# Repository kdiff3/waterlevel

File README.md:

# This is a PCB for a Capacitive Water Level Sensor

## License

This work is licensed under a Creative Commons Attribution-NonCommercial-ShareAlike 4.0 International License.

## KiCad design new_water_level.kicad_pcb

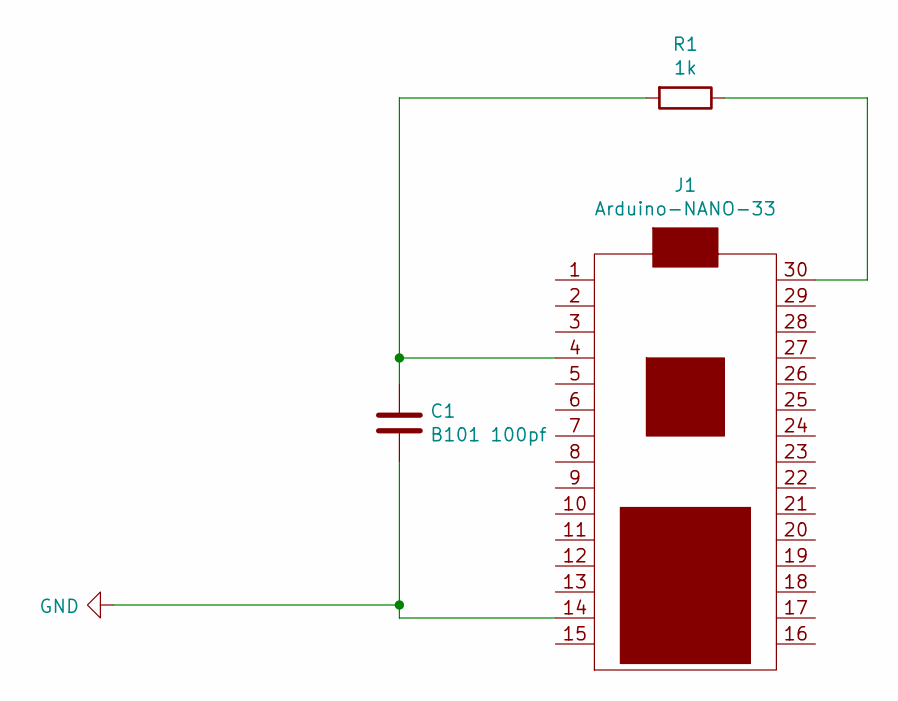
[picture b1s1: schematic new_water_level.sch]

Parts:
C1: B101 100pf; C_Disc_D5.0mm_W2.5mm_P5.00mm
J1: Arduino-NANO-33; NANO_33_Socket_Castell
R1: 1k; R_Axial_DIN0207_L6.3mm_D2.5mm_P10.16mm_Horizontal

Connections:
GND: C1.2, J1.14
unnamed: C1.1, J1.4, R1.2
unnamed: J1.30, R1.1

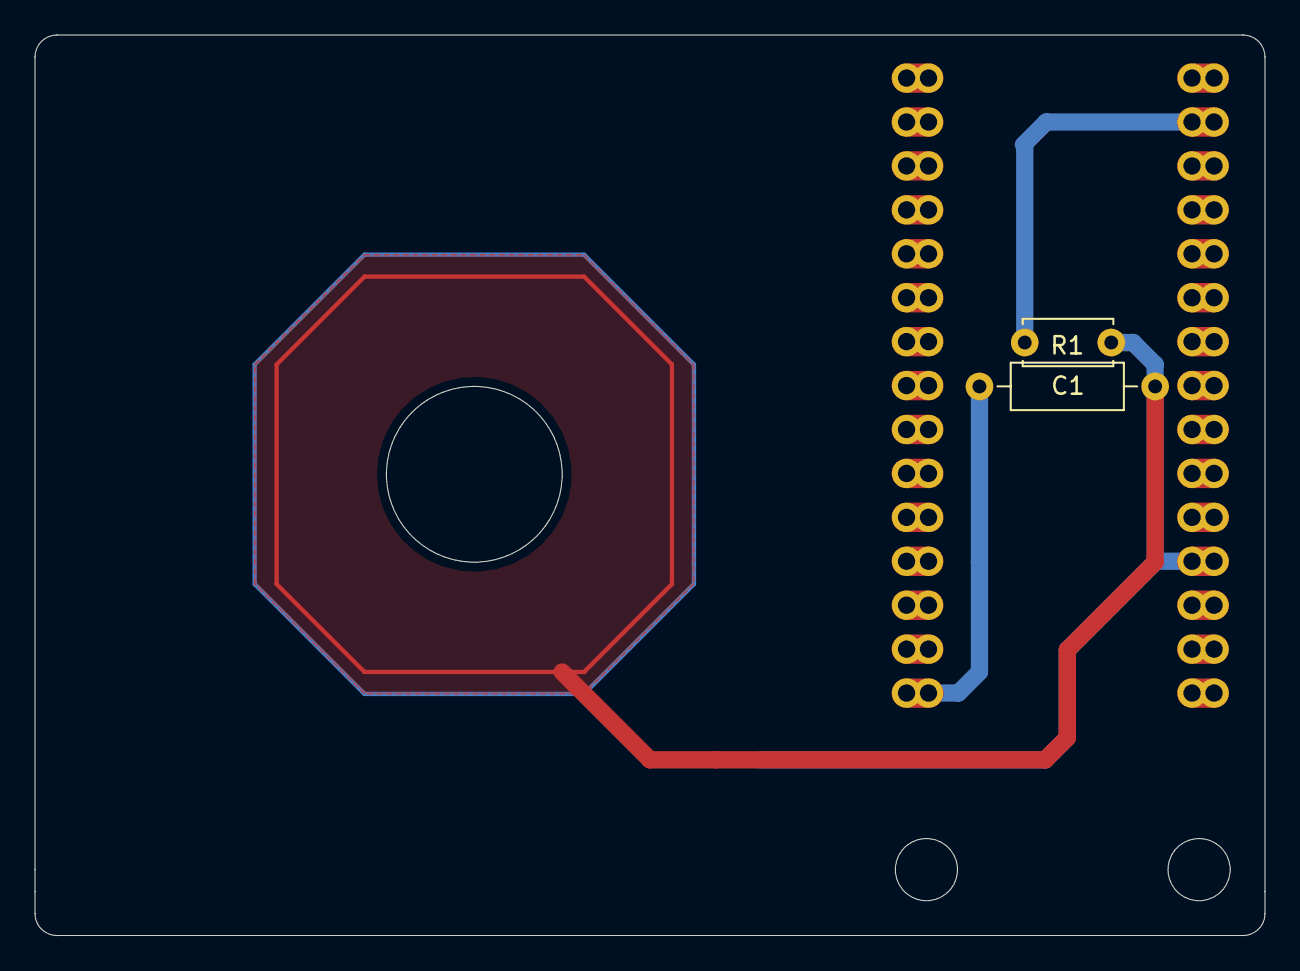
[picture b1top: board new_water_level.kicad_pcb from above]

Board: 2 copper layers, 71.1 x 52.1 mm, 3 parts (0 on the bottom side), 3 nets.

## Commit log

2021-07-05 - added PCB
